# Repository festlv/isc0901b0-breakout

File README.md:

# ISC0901B0 breakout board

ISC0901B0 is 336x256 microbolometer LWIR sensor manufactured by FLIR. 
Apparently it is being used in Tau2/Vue series camera cores, as well as many other FLIR products. 
Autoliv NV3 is also based on this sensor, and buying a second-hand, possibly damaged Autoliv NV3 module is probably the cheapest way to obtain such a sensor.

This breakout board connects directly to sensor and provides all the neccessary signals on 14-pin 2.54mm pin header (or IDC header).
It also generates the three required power rails: 2.5V for IO signals, 3.3V for core power and switchable 9/11V bias voltage.
Breakout board input voltage: 5V.
Sensor power consumption (incl. Iq of step-up convertor and LDO losses): approx 60-65mA at 5V input to breakout board.

# Sensor physical interface

All the signals described below are single ended, at VCC_IO of the sensor (2.5V in the Autoliv NV3).

**-> CLK:** clock for the sensor (nominal 73.636MHz for 60Hz). Sampling at other frequencies works, but the image is over/under exposed, as the CMD presumably configures the sensor for particular integration time.

**-> CMD:** synchronous command to sensor (output on rising edge). Bit order: MSB first. 

**-> BIAS:** synchronous bias data value to sensor. Each bias value is 7-bits long, so there is a value for each pixel. Bit order: LSB first

**-> ENA:** enable signal to sensor (?). High = sensor enabled, low = sensor disabled.

**<- DATA_0, DATA_1:** two data bits from sensor (output on falling edge, presumably sampled on rising). Each of the data lines represents a separate pixel. Bit order: LSB first.

# Startup sequence of Autoliv NV3

Measured without sensor:

1. all outputs low
2. start clk
3. 500uS delay
4. enable VCC_CORE (3.3V)
5. 15ms delay
6. enable VCC_IO (2.5V)
7. 4ms delay
8. enable VCC_BIAS (11.0V)

BIAS voltage at turn on = 11.0V

# Logical interface

After powerup sequence is finished, sensor needs to be enabled. 
Frame acquisition starts by sending a command preamble that consists of two bytes: [0x3f, 0xc0]. After that, a 20 byte sequence, of which several bytes seem to be specific to each sensor are sent.
After predetermined number of clock cycles, sensor starts responding with preamble 0x1555 on both data lines (repeating pattern of zeroes and ones).

One cycle after the sensor has started responding with preamble, bias values should be sent to sensor on the bias line: one 7-bit value for every pixel. The values are specific to each sensor: if a fixed value is sent, part of the pixels may appear to be non-responsive.
After preamble (two pixels), sensor sends the subsequent 336 pixels of image data. There is a horizontal blanking period after each line.
At the end of the readout (~256 lines), command must be sent again to initate sensor response.

The specific values for command and bias values appear to be stored in the encrypted regions of flash memory on Autoliv NV3. Further research is needed to determine if it's feasible to come up with
these values without access to flash memory contents of Autoliv NV3.

## Version history
* rev1 of this breakout board has been verified on Audi 4G0980552. 
  Observed issues: 
  * even with disabled boost converter, current path was provided by inductor.
  * outline of the PCB was slightly too large and did not fit the enclosure.
  * the 2.54mm header with just a single ground pin was very poor choice for an interface that runs at ~73MHz. It does work with ~5cm long cable though, but it's recommended to change to a different connector and add several more ground pins.

* rev2: fix first 2 problems mentioned above
* rev3: Changed the 2.54mm header with 20pin 0.5mm pitch FPC connector for better signal integrity.

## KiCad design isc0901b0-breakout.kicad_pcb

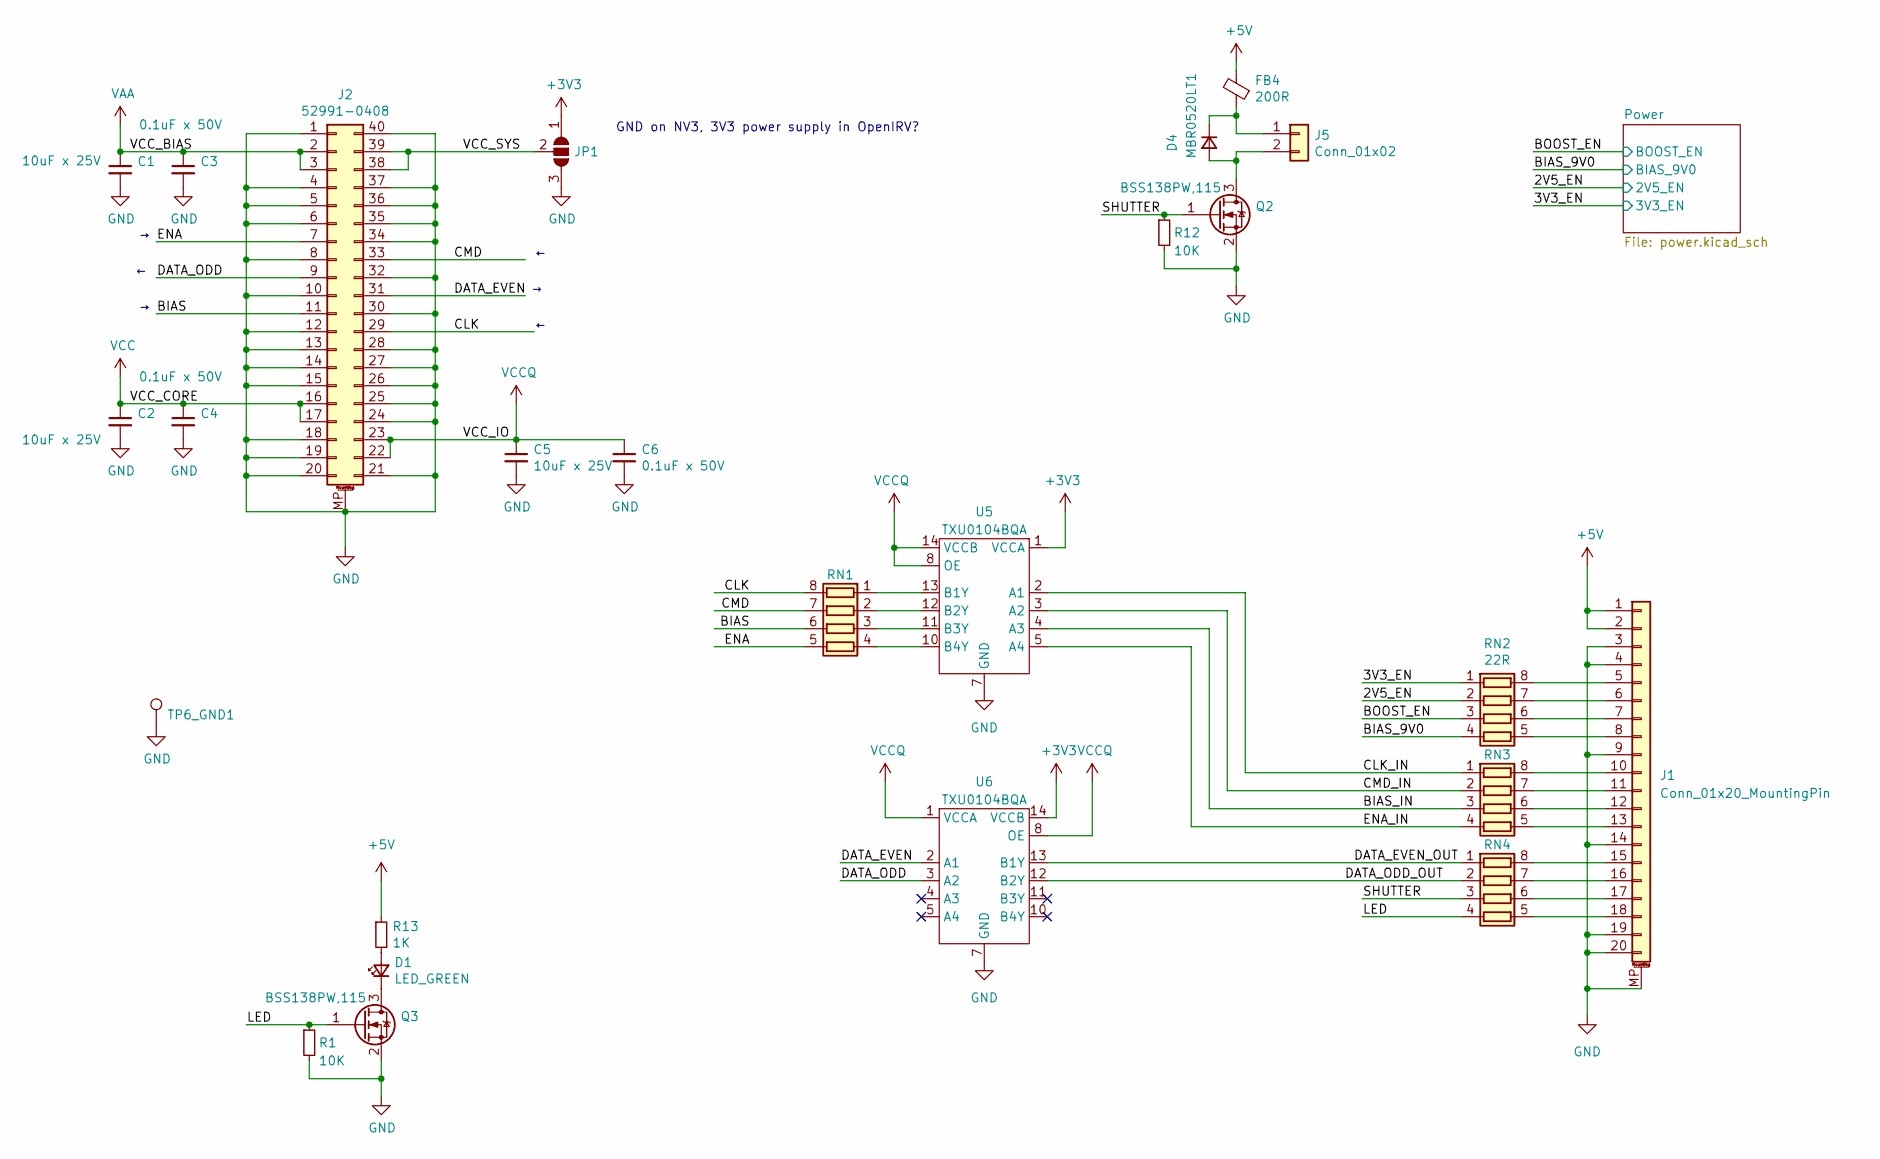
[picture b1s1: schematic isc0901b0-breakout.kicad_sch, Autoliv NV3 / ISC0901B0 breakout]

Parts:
C1, C2, C5: 10uF x 25V; C_0603_1608Metric; MPN GRT188R61E106ME13D
C3, C4, C6: 0.1uF x 50V; C_0603_1608Metric
D1: LED_GREEN; D_0603_1608Metric
D4: MBR0520LT1; D_SOD-123; MPN MBR0520LT1
FB4: 200R; L_0603_1608Metric
J1: Conn_01x20_MountingPin; X05C2020TZ; MPN X05C2020TZ
J2: 52991-0408; MPN 52991-0408
J5: Conn_01x02; JST_SH_BM02B-SRSS-TB_1x02-1MP_P1.00mm_Vertical; MPN BM02B-SRSS-TB(LF)(SN)
JP1: SolderJumper_3_Open; SolderJumper-3_P1.3mm_Open_Pad1.0x1.5mm
Q2, Q3: BSS138PW,115; SOT-323_SC-70; MPN BSS138PW,115
R1, R12: 10K; R_0603_1608Metric
R13: 1K; R_0603_1608Metric
RN1, RN2, RN3, RN4: 22R; R_Array_Concave_4x0603; MPN EXB-V8V220JV
TP6_GND1: TestPoint; TestPoint_Pad_D1.5mm
U5, U6: TXU0104BQA; TI_WFNQ-14_BQA; MPN TXU0104BQAR

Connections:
+3V3: JP1.1 (A), U5.1 (VCCA), U6.14 (VCCB); also elsewhere on the board
+5V: FB4.2, J1.1, J1.2, R13.1; also elsewhere on the board
/2V5_EN: RN2.2 (R2.1); also elsewhere on the board
/3V3_EN: RN2.1 (R1.1); also elsewhere on the board
/BIAS: J2.11, RN1.6 (R3.2)
/BIAS_9V0: RN2.4 (R4.1); also elsewhere on the board
/BIAS_IN: RN3.3 (R3.1), U5.4 (A3)
/BOOST_EN: RN2.3 (R3.1); also elsewhere on the board
/CLK: J2.29, RN1.8 (R1.2)
/CLK_IN: RN3.1 (R1.1), U5.2 (A1)
/CMD: J2.33, RN1.7 (R2.2)
/CMD_IN: RN3.2 (R2.1), U5.3 (A2)
/DATA_EVEN: J2.31, U6.2 (A1)
/DATA_EVEN_OUT: RN4.1 (R1.1), U6.13 (B1Y)
/DATA_ODD: J2.9, U6.3 (A2)
/DATA_ODD_OUT: RN4.2 (R2.1), U6.12 (B2Y)
/ENA: J2.7, RN1.5 (R4.2)
/ENA_IN: RN3.4 (R4.1), U5.5 (A4)
/LED: Q3.1 (G), R1.1, RN4.4 (R4.1)
/SHUTTER: Q2.1 (G), R12.1, RN4.3 (R3.1)
/VCC_SYS: J2.38, J2.39, JP1.2 (C)
GND: C1.2, C2.2, C3.2, C4.2, C5.2, C6.2, J1.3, J1.4, J1.9, J1.14, J1.19, J1.20, J1.MP (MountPin), J2.1, J2.4, J2.5, J2.6, J2.8, J2.10, J2.12, J2.13, J2.14, J2.15, J2.18, J2.19, J2.20, J2.21, J2.24, J2.25, J2.26, J2.27, J2.28, J2.30, J2.32, J2.34, J2.35, J2.36, J2.37, J2.40, J2.MP (MountPin), JP1.3 (B), Q2.2 (S), Q3.2 (S), R1.2, R12.2, TP6_GND1.1, U5.7 (GND), U6.7 (GND); also elsewhere on the board
unnamed: D1.1 (K), Q3.3 (D)
unnamed: D1.2 (A), R13.2
unnamed: D4.1 (K), FB4.1, J5.1
unnamed: D4.2 (A), J5.2, Q2.3 (D)
unnamed: J1.5, RN2.8 (R1.2)
unnamed: J1.6, RN2.7 (R2.2)
unnamed: J1.7, RN2.6 (R3.2)
unnamed: J1.8, RN2.5 (R4.2)
unnamed: J1.10, RN3.8 (R1.2)
unnamed: J1.11, RN3.7 (R2.2)
unnamed: J1.12, RN3.6 (R3.2)
unnamed: J1.13, RN3.5 (R4.2)
unnamed: J1.15, RN4.8 (R1.2)
unnamed: J1.16, RN4.7 (R2.2)
unnamed: J1.17, RN4.6 (R3.2)
unnamed: J1.18, RN4.5 (R4.2)
unnamed: RN1.1 (R1.1), U5.13 (B1Y)
unnamed: RN1.2 (R2.1), U5.12 (B2Y)
unnamed: RN1.3 (R3.1), U5.11 (B3Y)
unnamed: RN1.4 (R4.1), U5.10 (B4Y)
VAA: C1.1, C3.1, J2.2, J2.3; also elsewhere on the board
VCC: C2.1, C4.1, J2.16, J2.17; also elsewhere on the board
VCCQ: C5.1, C6.1, J2.22, J2.23, U5.8 (OE), U5.14 (VCCB), U6.1 (VCCA), U6.8 (OE); also elsewhere on the board

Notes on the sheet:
GND on NV3, 3V3 power supply in OpenIRV?

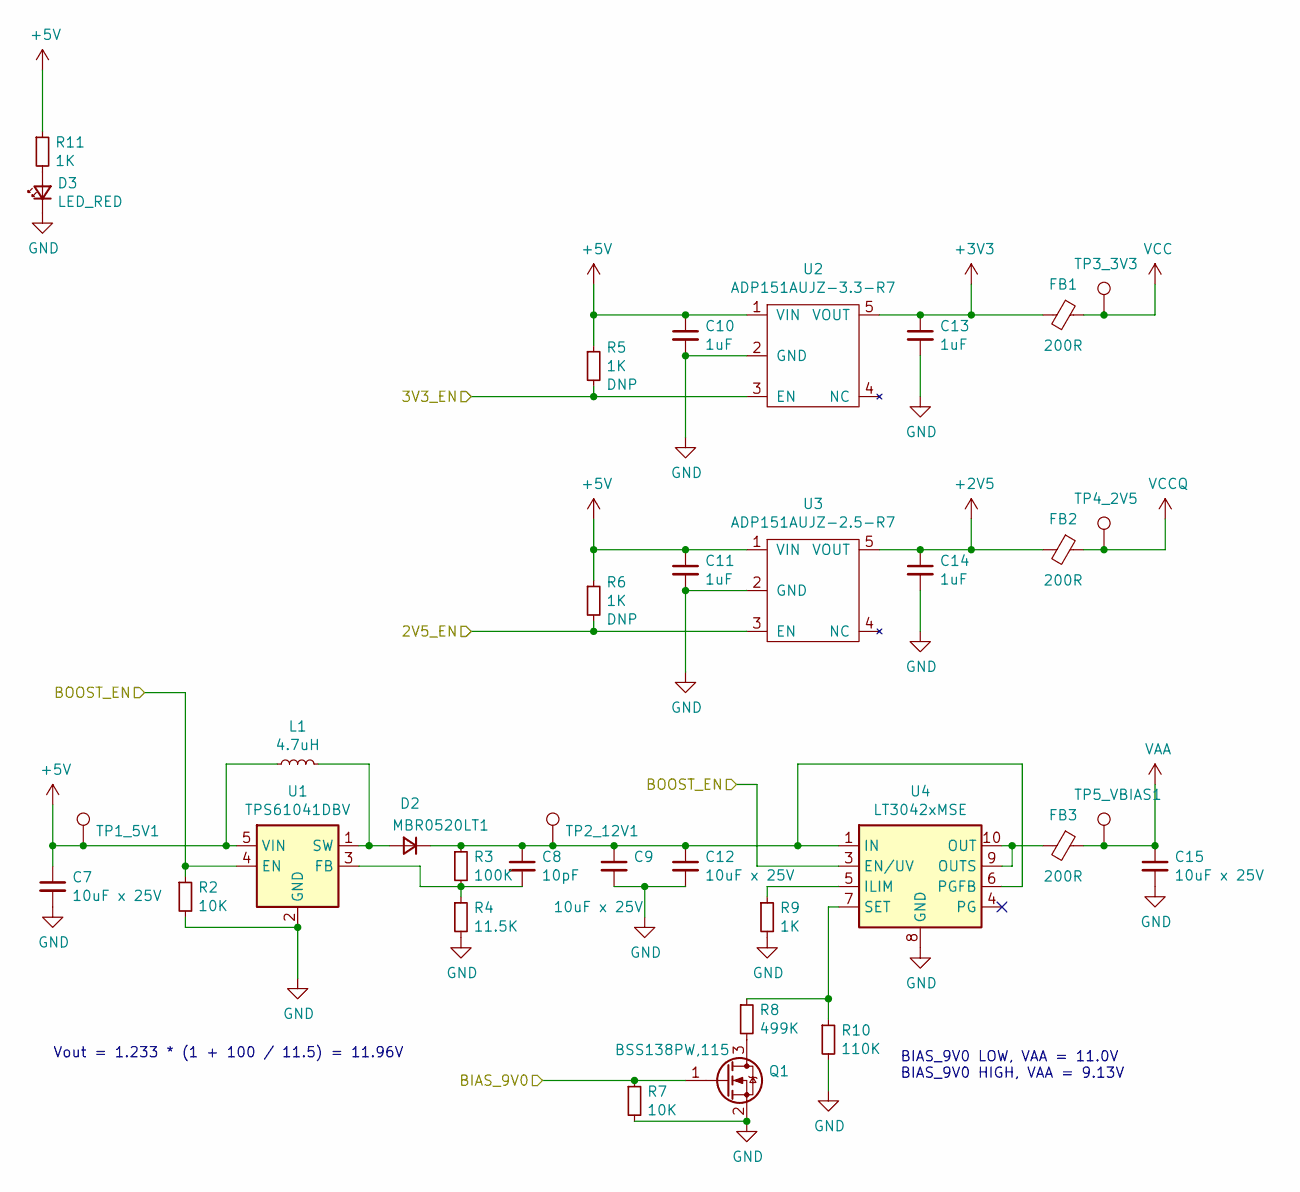
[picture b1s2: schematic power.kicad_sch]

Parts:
C7, C9, C12, C15: 10uF x 25V; C_0603_1608Metric; MPN GRT188R61E106ME13D
C8: 10pF; C_0603_1608Metric
C10, C11, C13, C14: 1uF; C_0603_1608Metric
D2: MBR0520LT1; D_SOD-123
D3: LED_RED; D_0603_1608Metric
FB1, FB2, FB3: 200R; L_0603_1608Metric
L1: 4.7uH; L_0805_2012Metric
Q1: BSS138PW,115; SOT-323_SC-70; MPN BSS138PW,115
R2, R7: 10K; R_0603_1608Metric
R3: 100K; R_0603_1608Metric
R4: 11.5K; R_0603_1608Metric
R5, R6, R9, R11: 1K; R_0603_1608Metric
R8: 499K; R_0603_1608Metric
R10: 110K; R_0603_1608Metric
TP1_5V1, TP2_12V1, TP3_3V3, TP4_2V5, TP5_VBIAS1: TestPoint; TestPoint_Pad_D1.5mm
U1: TPS61041DBV; SOT-23-5; MPN TPS61041DBV
U2: ADP151AUJZ-3.3-R7; TSOT-23-5; MPN ADP151AUJZ-3.3-R7
U3: ADP151AUJZ-2.5-R7; TSOT-23-5; MPN ADP151AUJZ-2.5-R7
U4: LT3042xMSE; MSOP-10-1EP_3x3mm_P0.5mm_EP1.68x1.88mm; MPN LT3042EMSE#PBF

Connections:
+2V5: C14.1, FB2.2, U3.5 (VOUT)
+3V3: C13.1, FB1.2, U2.5 (VOUT); also elsewhere on the board
+5V: C7.1, C10.1, C11.1, L1.1, R5.1, R6.1, R11.1, TP1_5V1.1, U1.5 (VIN), U2.1 (VIN), U3.1 (VIN); also elsewhere on the board
/2V5_EN: R6.2, U3.3 (EN); also elsewhere on the board
/3V3_EN: R5.2, U2.3 (EN); also elsewhere on the board
/BIAS_9V0: Q1.1 (G), R7.1; also elsewhere on the board
/BOOST_EN: R2.1, U1.4 (EN), U4.3 (EN/UV); also elsewhere on the board
GND: C7.2, C9.2, C10.2, C11.2, C12.2, C13.2, C14.2, C15.2, D3.1 (K), Q1.2 (S), R2.2, R4.2, R7.2, R9.2, R10.2, U1.2 (GND), U2.2 (GND), U3.2 (GND), U4.8 (GND), U4.11 (GND); also elsewhere on the board
unnamed: C8.2, R3.2, R4.1, U1.3 (FB)
unnamed: C8.1, C9.1, C12.1, D2.1 (K), R3.1, TP2_12V1.1, U4.1 (IN), U4.2 (IN), U4.6 (PGFB)
unnamed: D2.2 (A), L1.2, U1.1 (SW)
unnamed: D3.2 (A), R11.2
unnamed: FB3.2, U4.9 (OUTS), U4.10 (OUT)
unnamed: Q1.3 (D), R8.2
unnamed: R9.1, U4.5 (ILIM)
unnamed: R8.1, R10.1, U4.7 (SET)
VAA: C15.1, FB3.1, TP5_VBIAS1.1; also elsewhere on the board
VCC: FB1.1, TP3_3V3.1; also elsewhere on the board
VCCQ: FB2.1, TP4_2V5.1; also elsewhere on the board

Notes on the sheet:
BIAS_9V0 LOW, VAA = 11.0V BIAS_9V0 HIGH, VAA = 9.13V
Vout = 1.233 * (1 + 100 / 11.5) = 11.96V

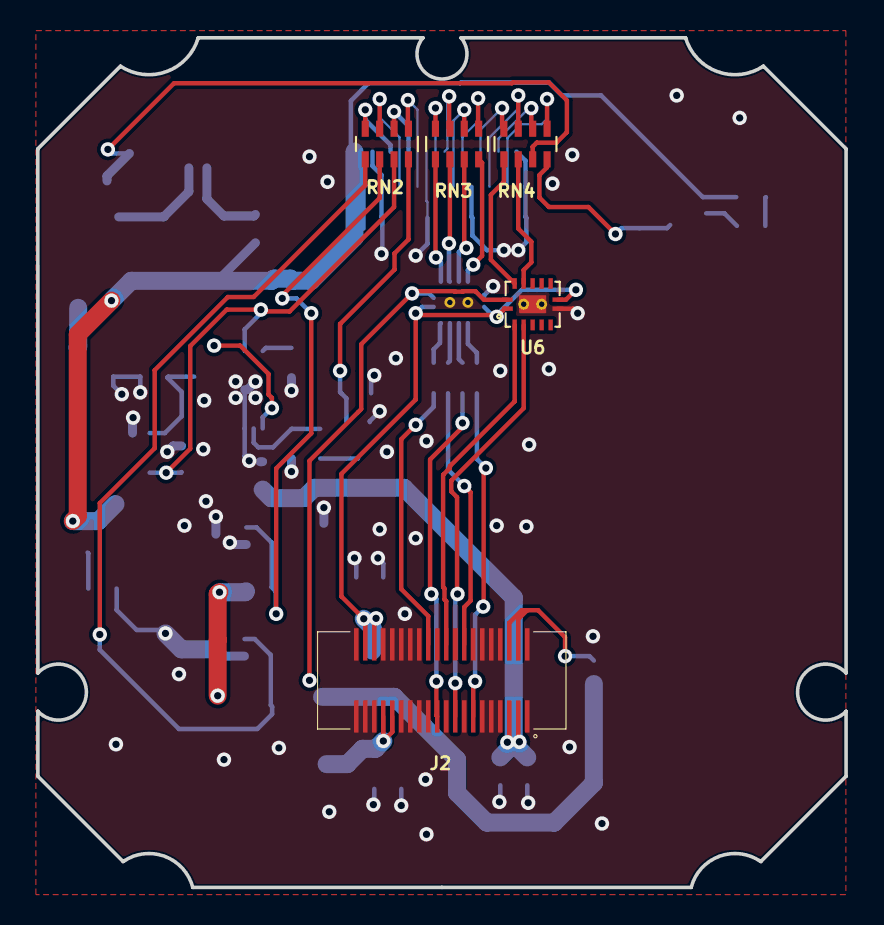
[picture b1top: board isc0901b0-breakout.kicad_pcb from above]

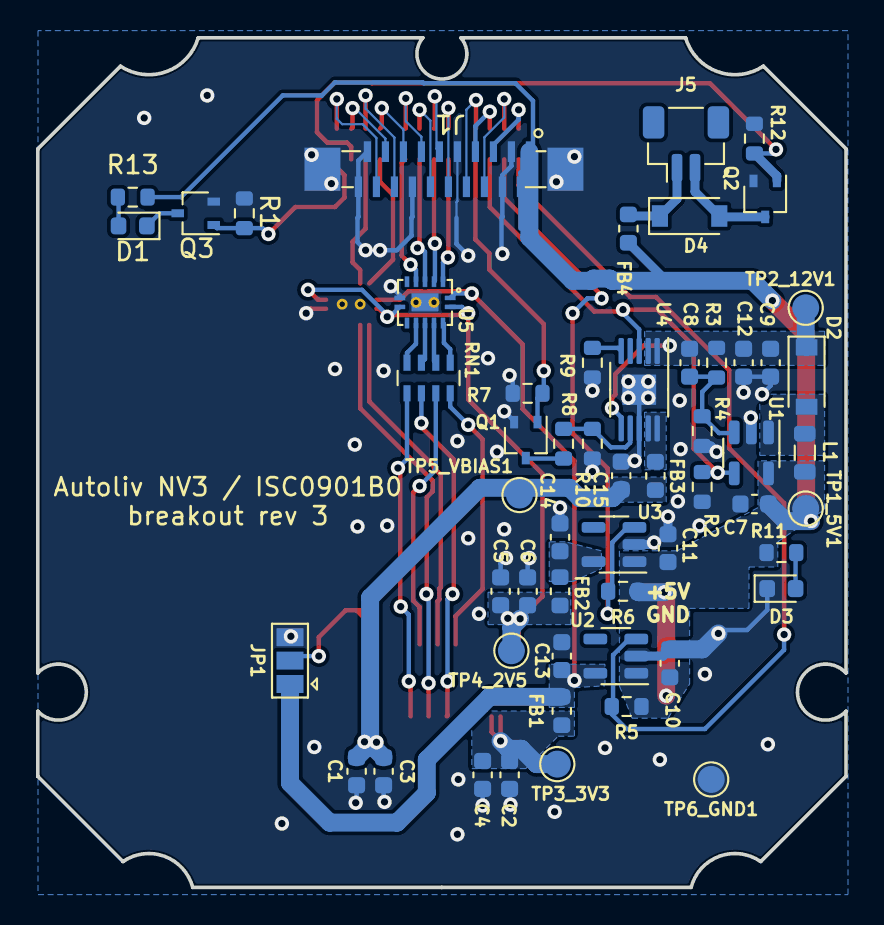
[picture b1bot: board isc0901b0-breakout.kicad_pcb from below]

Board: 2 copper layers, 44.9 x 47.2 mm, 60 parts (55 on the bottom side), 54 nets.

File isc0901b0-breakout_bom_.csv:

Component,Description,Part,References,Value,Footprint,Quantity Per PCB,Datasheet,MPN,Manufacturer,Config
1,"Unpolarized capacitor, small symbol",C_Small,C8,10pF,C_0603_1608Metric,1,~,,,
2,"Unpolarized capacitor, small symbol",C_Small,C10 C11 C13 C14,1uF,C_0603_1608Metric,4,~,,,
3,"Unpolarized capacitor, small symbol",C_Small,C3 C4 C6,0.1uF x 50V,C_0603_1608Metric,3,~,,,
4,"Unpolarized capacitor, small symbol",C_Small,C1 C2 C5 C7 C9 C12 C15,10uF x 25V,C_0603_1608Metric,7,~,GRT188R61E106ME13D,Murata,
5,"Light emitting diode, small symbol",LED_Small,D1 D3,LED_RED,D_0603_1608Metric,2,~,,,
6,"Diode, small symbol",D_Small,D2 D4,MBR0520LT1,D_SOD-123,2,~,MBR0520LT1,,
7,"Ferrite bead, small symbol",Ferrite_Bead_Small,FB1 FB2 FB3 FB4,200R,L_0603_1608Metric,4,~,,,
8,"Generic connectable mounting pin connector, double row, 02x20, counter clockwise pin numbering scheme (similar to DIP packge numbering), script generated (kicad-library-utils/schlib/autogen/connector/)",Conn_02x20_Counter_Clockwise_MountingPin,J2,52991-0408,52991-0408,1,~,52991-0408,,
9,"Generic connector, single row, 01x02, script generated (kicad-library-utils/schlib/autogen/connector/)",Conn_01x02,J3,Conn_01x02,PinHeader_1x02_P2.54mm_Vertical,1,~,,,
10,"Generic connector, single row, 01x02, script generated (kicad-library-utils/schlib/autogen/connector/)",Conn_01x02,J5,Conn_01x02,JST_SH_BM02B-SRSS-TB_1x02-1MP_P1.00mm_Vertical,1,~,BM02B-SRSS-TB(LF)(SN),JST,
11,"Generic connector, double row, 02x07, odd/even pin numbering scheme (row 1 odd numbers, row 2 even numbers), script generated (kicad-library-utils/schlib/autogen/connector/)",Conn_02x07_Odd_Even,J4,IDC_02x07,IDC-Header_2x07_P2.54mm_Vertical,1,~,302-S141,On Shore Technology Inc.,
12,"Inductor, small symbol",L_Small,L1,4.7uH,L_0805_2012Metric,1,~,,,
13,"N-MOSFET transistor, gate/source/drain",Q_NMOS_GSD,Q1 Q2,"BSS138PW,115",SOT-323_SC-70,2,~,"BSS138PW,115",,
14,"Resistor, small symbol",R_Small,R1 R11,1K,R_0603_1608Metric,2,~,,,
15,"Resistor, small symbol",R_Small,R2 R7 R12,10K,R_0603_1608Metric,3,~,,,
16,"Resistor, small symbol",R_Small,R4,11.5K,R_0603_1608Metric,1,~,,,
17,"Resistor, small symbol",R_Small,R3,100K,R_0603_1608Metric,1,~,,,
18,"Resistor, small symbol",R_Small,R10,110K,R_0603_1608Metric,1,~,,,
19,"Resistor, small symbol",R_Small,R8,499K,R_0603_1608Metric,1,~,,,
20,"4 resistor network, parallel topology",R_Pack04,RN1 RN2 RN3,22R,R_Array_Concave_4x0603,3,~,EXB-V8V220JV,,
21,,ADP151,U3,ADP151AUJZ-2.5-R7,TSOT-23-5,1,,ADP151AUJZ-2.5-R7,,
22,,ADP151,U2,ADP151AUJZ-3.3-R7,TSOT-23-5,1,,ADP151AUJZ-3.3-R7,,
23,"200mA, Adjustable, Ultralow Noise, Ultrahigh PSRR RF Linear Regulator, MSOP-10",LT3042xMSE,U4,LT3042xMSE,MSOP-10-1EP_3x3mm_P0.5mm_EP1.68x1.88mm,1,https://www.analog.com/media/en/technical-documentation/data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,LT3042EMSE#PBF,,
24,"Synchronous Boost Regulator, Adjustable Output up to 28V, 250 mA Switch Current Limit, SOT-23-5",TPS61041DBV,U1,TPS61041DBV,SOT-23-5,1,http://www.ti.com/lit/ds/symlink/tps61040.pdf,TPS61041DBV,,





Component Groups:,26
Component Count:,50
Fitted Components:,46
Number of PCBs:,1
Total components:,46
Schematic Version:,
Schematic Date:,
PCB Variant:,['default']
BoM Date:,"pirmdiena, 2021. gada 19. aprīlis, 15:43:23"
Schematic Source:,ics0901b0-breakout.sch
KiCad Version:,Eeschema 5.1.9-73d0e3b20d~88~ubuntu20.04.1

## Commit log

2021-05-19 Initial commit with rev2.
2021-05-19 Create LICENSE
2021-05-19 Add information on sensor interface
2021-05-20 Add .gitignore
2022-01-19 Finished rev3 of the board with 20pin FPC connector
